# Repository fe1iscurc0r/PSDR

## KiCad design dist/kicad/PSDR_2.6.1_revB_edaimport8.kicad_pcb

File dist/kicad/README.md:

# PSDR 2.6.1 KiCad schematic

KiCad 10 schematic for the PSDR 2.6.1 main board (STM32F746/F429 HF SDR,
0-35 MHz). It is generated from the 2.6.1 PADS Layout ASCII netlist and laid
out one sheet per page of the 2016-07-31 schematic PDF.

## Why this exists

`master` ships the PADS Logic/Layout binaries (`Hardware/PSDR.sch`,
`Hardware/PSDR.pcb`) and an 8-page 2014 schematic PDF. The 2.6.1 ASCII
(`Hardware/PSDR.asc`) and the 10-page 2016 PDF are only on `PSDR_Rebuild` /
`PSDR_F7` / `PSDR_F7_DMA` at `468dc41`. No KiCad-native schematic existed, so
the design could not be opened, searched or checked without PADS.

## What it is, and what it is not

Every pin gets a global label carrying its PADS net name, placed exactly at the
pin endpoint. Pins with no net get a no-connect flag. There are **no wires**:
the connectivity is carried entirely by labels.

This is a **connectivity model, not redrawn artwork**. Trace shapes, symbol
graphics and the designer's margin notes live only in
`Hardware/PSDR_2.6.1_Schematic_2016-07-31.pdf` (page N here corresponds to PDF
page N). It is meant to be read next to that PDF, and to make the netlist
machine-checkable.

## Contents

| File | Contents |
|---|---|
| `PSDR_2.6.1.kicad_sch` | Root sheet, A2, nine hierarchical sheets |
| `PSDR_2.6.1-p02..p10.kicad_sch` | One sheet per PDF page, 391 parts total |
| `PSDR_2.6.1.kicad_sym` | 57 reconstructed symbols (one per PADS part type) |
| `PSDR_2.6.1.kicad_pro`, `sym-lib-table` | Project and symbol library wiring |
| `../netlist/PSDR_2.6.1_netlist.csv` | `net,refdes,pin,pin_name,part_type`, 1132 rows |
| `../netlist/PSDR_2.6.1_netlist.json` | Same data plus the 41 unconnected pins |

Page map: 2 MCU/GPS/USB, 3 clock (Si5338), 4 analog switches/drivers,
5 RX/TX baseband, 6 audio/microphone, 7 UI paddles/LEDs/LCD, 8 power,
9 RF front end, 10 variable filter. PDF page 1 carries notes only, so there is
no sheet for it.

## Regenerating

Requires Python 3 (standard library only) and KiCad 10 for the checks.

```
python tools/pads_asc_to_kicad.py --asc Hardware/PSDR.asc \
    --pdf Hardware/PSDR_2.6.1_Schematic_2016-07-31.pdf \
    --out dist/kicad
```

UUIDs are derived with `uuid5(NAMESPACE_URL, "psdr261/...")`, so the same input
produces byte-identical output; a diff after regeneration is a real change.

`--pcb FILE` optionally copies the footprint field from a `.kicad_pcb` (the
PADS decal name, e.g. `PSDR_PADS:CAP_0603`). Without it that one property is
empty; nothing else changes (391 lines out of ~104000). The board itself is
not part of this change: `.emn`/`.emp` carry only outline, holes and placement,
so the reconstructed board has no pads for 366 of 391 parts and no routing.

## Verification

```
python tools/pads_asc_netlist.py Hardware/PSDR.asc \
    --csv dist/netlist/PSDR_2.6.1_netlist.csv \
    --json dist/netlist/PSDR_2.6.1_netlist.json

kicad-cli sch export netlist --format kicadxml -o out.xml dist/kicad/PSDR_2.6.1.kicad_sch
python tools/kicad_netlist_compare.py --pads dist/netlist/PSDR_2.6.1_netlist.json --kicad out.xml

python tools/kicad_sch_geomcheck.py dist/kicad/PSDR_2.6.1.kicad_sch
kicad-cli sch erc --severity-all dist/kicad/PSDR_2.6.1.kicad_sch
```

Results:

- Netlist: 278 of 278 PADS nets have identical pin sets, 1132 of 1132 connected
  pins are covered, 0 nets only on one side, 0 pins in more than one net,
  391 components. The comparison is a partition check, not a name check, so a
  short between two nets fails it.
- Geometry: no two connection points coincide in any of the 10 files (1173
  points = 1132 labels + 41 no-connects). This is checked separately because
  KiCad silently merges coincident pins and the netlist export would not show it.
- ERC: 0 errors, 391 warnings, all `footprint_link_issues` because the
  `PSDR_PADS` footprint library is deliberately not shipped.
- Names: 276 of 278 match character for character. The other two differ only by
  the PADS overbar escape: `AUDIO_AMP_\SHDN` -> `AUDIO_AMP_~{SHDN}`,
  `\EARPHONE_INSERTED` -> `~{EARPHONE_INSERTED}`.

The exported XML netlist differs between runs only in its `<date>` element.

## Known limits

- Eleven one-pin test pads have ambiguous refdes text in the PDF (`+`, `-`,
  `1PPS`, `CLK`, `DAC1`, `DAC2`, `GND`, `LIPO`, `NRST`, `SCL`, `SDA`). They are
  placed in a strip at the bottom of their page. Connectivity is unaffected: the
  netlist is keyed by refdes, not by position.
- No hierarchical sheet pins. Global labels already connect across sheets.
- No footprint library is shipped, hence the 391 ERC warnings.

## Provenance

- `Hardware/PSDR.asc`: PSDR 2.6.1 PADS Layout ASCII, upstream `468dc41`
  (`Hardware/PSDR.asc`).
- `Hardware/PSDR_2.6.1_Schematic_2016-07-31.pdf`: upstream `468dc41`
  (`Hardware/PSDR Schematic.pdf`), 10 pages, `CreationDate` 2016-07-26.
- Netlist extraction and the sheet layout follow the rules in
  `tools/pads_asc_netlist.py` and `tools/pads_asc_to_kicad.py`.

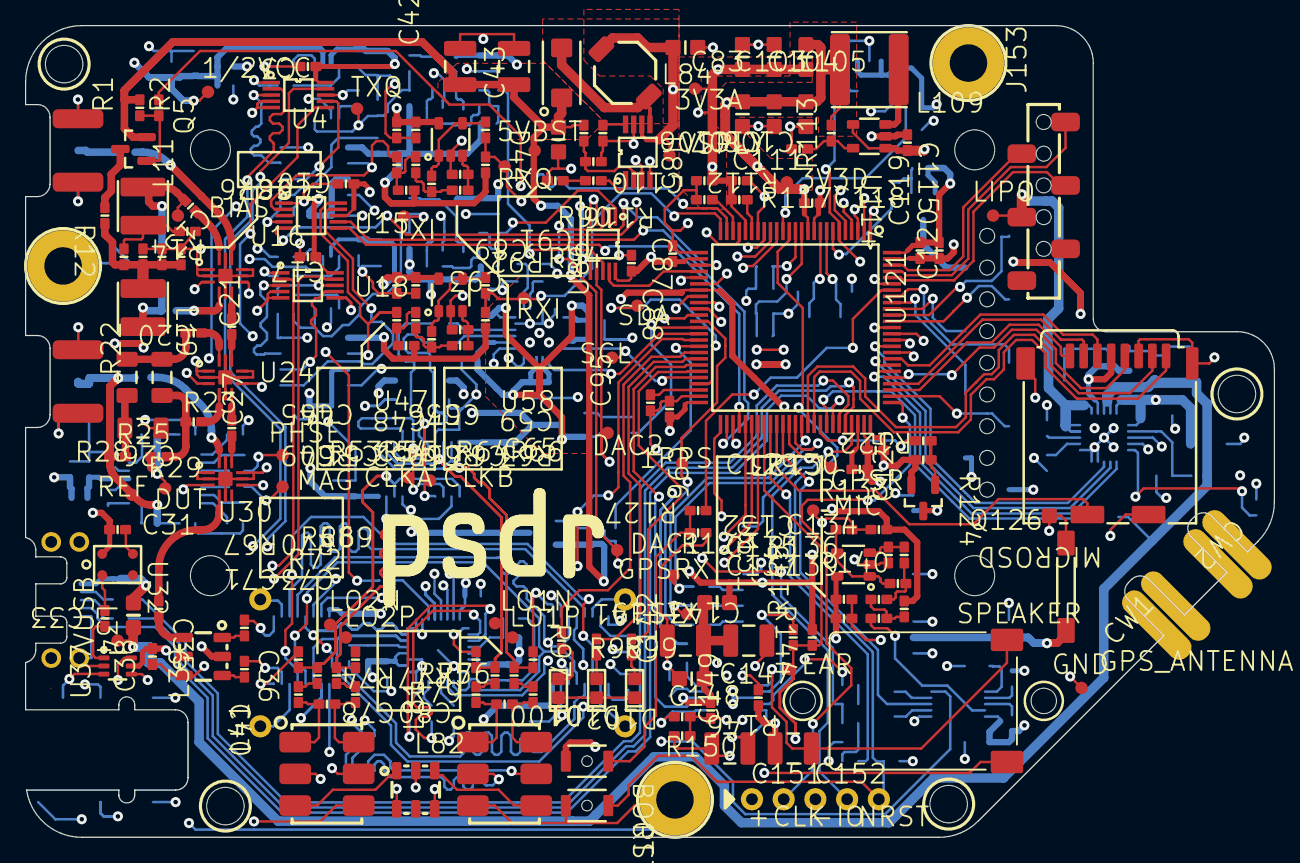
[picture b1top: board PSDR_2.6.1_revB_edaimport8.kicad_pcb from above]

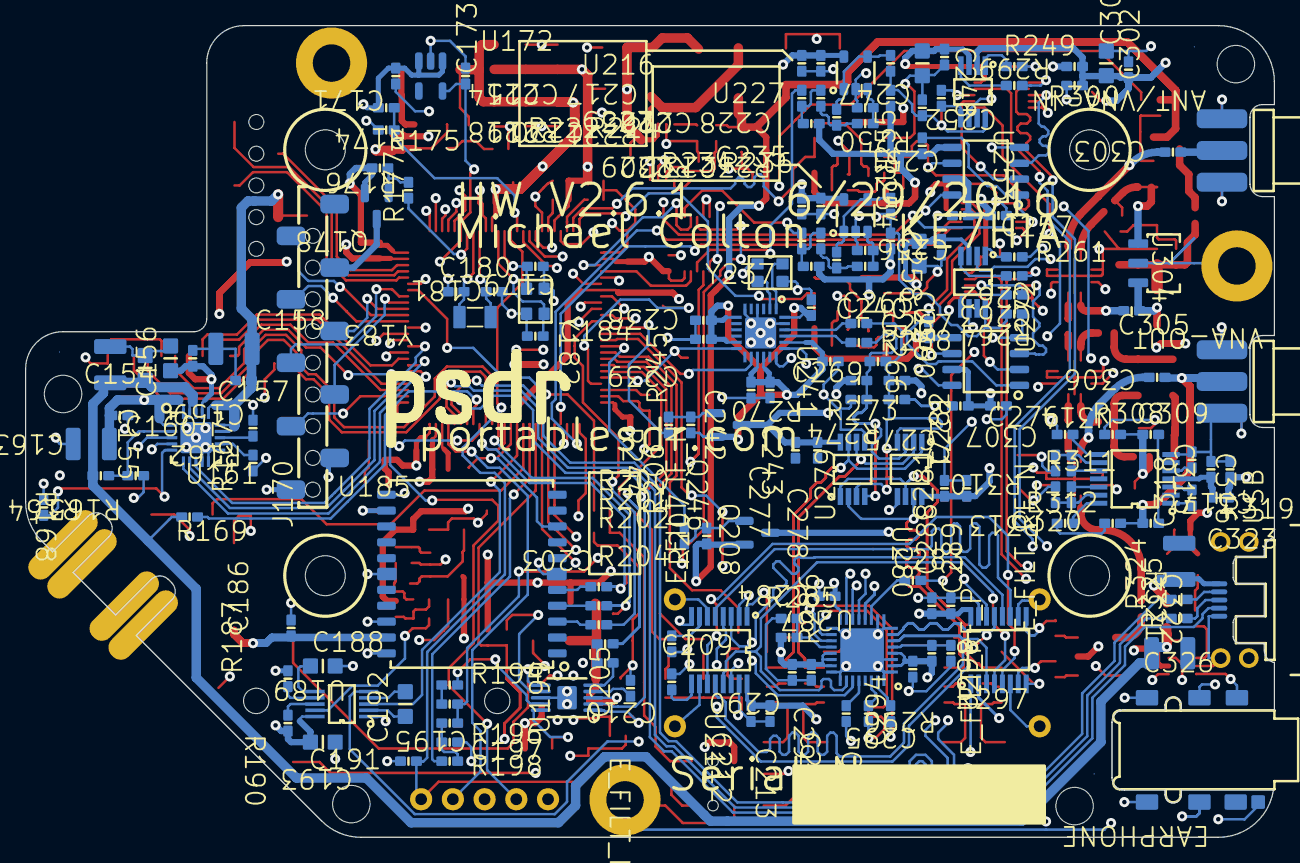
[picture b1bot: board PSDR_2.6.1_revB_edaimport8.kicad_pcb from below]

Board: 4 copper layers, 100.0 x 65.0 mm, 391 parts (182 on the bottom side), 277 nets.

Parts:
1/2VCC, 1PPS, 3V3A, 3V3D, 5VBST: PAD_1MM
+: 0.1in_1PIN
-: 0.1in_1PIN
ANT/VNA-IN: SMA_BOARD_EDGE
BIAS: PAD_1MM
BOOT: BUTTON_B3U-1000P-B
C3, C7, C8, C9, C10, C13, C17, C20, C21, C26, C27, C31, C33, C35, C36, C38, C40, C45, C46, C48, C49, C51, C54, C56, C57, C59, C60, C62, C65, C71, C73, C78, C80, C87, C88, C91, C93, C95, C96, C110, C111, C115, C118, C119, C120, C123, C125, C129, C132, C134, C135, C137, C139, C148, C149, C157, C159, C160, C171, C173, C179, C180, C181, C184, C186, C193, C195, C197, C203, C205, C209, C210, C212, C213, C214, C215, C217, C218, C220, C223, C225, C226, C228, C229, C231, C235, C238, C239, C240, C242, C243, C248, C251, C252, C256, C257, C259, C262, C263, C265, C267, C269, C275, C276, C277, C278, C281, C282, C283, C284, C288, C289, C290, C291, C292, C293, C294, C295, C302, C303, C305, C306, C307, C309, C315, C316, C317, C318, C320, C322: CAP_0603
C42, C43, C142, C143, C151, C152, C154, C158, C163, C323, C326: CSM-X5R-22U-20P-10V-1210
C83: CSM-X5R-10U0-10P-10V-0805
C89, C103, C104, C106, C107, C108, C156: CAP_0805
C147, C155, C188, C191, C192, C247, C258: CSM-X5R-10U0-10P-25V-0805
C301: CSM-X5R-47U-20P-6V3-0805
CLK: 0.1in_1PIN
CLKA: PAD_1MM
CLKB: PAD_1MM
CW1, CW2: MORSE_PADDLE_CONTACTS
D44: DIODE-SMA
D100, D101, D102: LED_0603
DAC1, DAC2: PAD_1MM
DUT: PAD_1MM
EAR: PAD_1MM
EARPHONE: 3.5MM_PHONO_4P_3SW_SJ-42617-SMT
E_FILT_IF_N: 0.1in_1PIN
E_FILT_IF_P: 0.1in_1PIN
E_FILT_RF_N: 0.1in_1PIN
E_FILT_RF_P: 0.1in_1PIN
F1, F2, F3, F4, F5, F6: FIDUCIAL_1MM
GND: PAD_1MM
GPSR: PAD_1MM
GPSRX: PAD_1MM
GPSTX: PAD_1MM
GPS_ANTENNA: GPS_ANTENNA-W3062A
IO: 0.1in_1PIN
J153: 0.1in_6P_HEADER_DUAL_ENTRY_1241152-6
J170: SPI_LCD_BOTTOM_ENTRY
L11, L19: IND_SMT_220UH_SRN4018-221M
L34, L105, L141: ISM-0805-10U
L39, L82: BALUN_1-2_WBC2-1TL
L41, L81: MIXER_DIODE-RING_ADE-2ASK
L84: IND_4.7UH_SMT_CDRH4D28CNP-4R7PC
L109: 2U2H_INDUCTOR_NR6028T2R2N
LIPO: PAD_1MM
LO1N, LO1P, LO2N, LO2P: PAD_1MM
M1, M2, M3: MH3M_PLATED
M4, M5, M6, M7: MH3M
MAG: PAD_1MM
MIC: PAD_1MM
MICROSD: MICROSD_DM3CS-SF
NRST: 0.1in_1PIN
PHSE: PAD_1MM
Q5, Q126, Q178, Q208, Q246: MOSFET_P_SOT23_IRLML6401
R1, R2, R6, R12, R14, R28, R29, R50, R52, R53, R55, R61, R63, R64, R66, R67, R68, R69, R70, R72, R74, R75, R76, R77, R79, R90, R92, R94, R97, R98, R99, R112, R113, R116, R117, R122, R124, R127, R128, R130, R133, R136, R140, R144, R145, R146, R150, R162, R164, R165, R167, R168, R169, R174, R175, R176, R177, R187, R190, R194, R196, R198, R200, R201, R202, R204, R206, R207, R219, R221, R222, R224, R230, R232, R234, R236, R244, R245, R249, R250, R254, R261, R264, R266, R268, R270, R271, R273, R274, R285, R286, R296, R297, R299, R300, R308, R310, R311, R312, R313, R319, R321, R324, R325: RES_0603
R22, R23, R25: RSM-6K98-1PCT-250MW-1206
REF: PAD_1MM
RST: BUTTON_B3U-1000P-B
RXI: PAD_1MM
RXQ: PAD_1MM
SCL: PAD_1MM
SDA: PAD_1MM
SPEAKER: SPEAKER_SMT_WATERPROOF_2403-260-00107
TXI: PAD_1MM
TXQ: PAD_1MM
U4, U18, U86: DPDT_ANALOG_MAX4525
U15: DIGITAL_POT_MAX5388
U16, U24, U30: RF_DPDT_MASWSS0129TR
U32: MICROPHONE_MEMS_SPU0410HR5H-PB
U37: SPDT_ANALOG_SWITCH_SN74LVC1G3157
U47, U58, U131, U216, U227: OP_AMP_FAN4174
U85: BOOST_REG_ADP1613
U114: BUCK_REGULATOR_AP3417C
U121: STM32F746_LQFP100
U161: BAT-MANAGE_MCP73871
U172: 3V3_LDO_MCP1802
U185: GPS_MODULE_RXM-GPS-RM-T
U189: MIC_PREAMP_SSM2167
U199: AUDIO_AMP_TPA0253DGQR
U211, U298: 74CBTLV3253
U241: SI5338
U253, U260: AD8131
U255, U272: MCP6N11
U279, U280: SY10EP52V
U287: VARIABLE_FILTER_HMC1023
U304: MMIC-AMP_HMC482ST
U314: AD8302
USB: MICROUSB_H12192CT-ND
VNA-OUT: SMA_BOARD_EDGE
VSPLY: PAD_1MM
VUSB: PAD_1MM
X1, X2: MH_80M
Y182, Y237: CRYSTAL3225
Y183: CRYSTAL_SMT_32.768

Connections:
5V_REG_ENABLE: U85.3, U121.1
$$$484: Q126.1, R122.1, R124.1
$$$596: R312.1, R313.2, U314.13
$$$598: R22.1, R25.2, R28.2
$$$618: Q178.1, R176.1, R177.2
$$$1054: C316.2, R319.1, U314.4
$$$1603: C322.2, U314.2
$$$1611: C309.2, U314.6
$$$1679: C188.1, U189.6
$$$1694: C318.2, U314.3
$$$1701: C315.2, U314.5
$$$1734: C192.2, U189.4
$$$1740: C192.1, U189.2
$$$2458: C320.2, U314.14
$$$2472: C307.1, U314.8
$$$2878: R311.1, U314.10
$$$2881: R310.1, R311.2, U314.9
$$$2891: R313.1, U314.12
$$$2987: C197.1, R196.1, R198.2
$$$3254: R190.1, U189.8
$$$3258: R187.1, U189.7
$$$4060: Q5.1, R1.2, R2.2
$$$5312: C139.2, R136.1, R140.1
$$$5393: U241.2, Y237.1
$$$5395: U241.1, Y237.3
$$$5476: C134.2, R133.1, R136.2
$$$5477: E_FILT_IF_P.1, U211.10
$$$5480: E_FILT_IF_N.1, U211.6
$$$5486: E_FILT_RF_P.1, U298.6
$$$5490: E_FILT_RF_N.1, U298.10
$$$5502: C132.1, R133.2, U131.3
$$$5510: C265.1, U241.22
$$$5513: C267.1, U241.21
$$$5711: C129.1, C134.1, U131.1, U131.4
$$$5934: LO1N.1, R74.2, R75.2, U279.6, U280.2
$$$5936: LO2P.1, R69.2, R70.2, U279.2, U280.7
$$$5937: LO2N.1, R67.2, R68.2, U279.1, U280.6
$$$5939: LO1P.1, R76.2, R77.2, U279.7, U280.1
$$$8723: L41.3, L82.1
$$$8785: L81.4, L82.3
$$$8887: C148.1, U199.1
$$$9133: Q208.1, R206.1, R207.2
$$$9448: L41.5, U4.9
$$$9458: L41.2, U4.2
$$$9485: L81.5, U18.9
$$$9489: L81.2, U18.2
$$$9652: R194.2, U199.9
$$$9661: R204.2, U199.5
$$$9712: C195.2, R194.1
$$$9714: C203.2, R204.1
$$$9819: C152.2, EARPHONE.3, R146.2
$$$9979: EARPHONE.10, SPEAKER.2
$$$10136: C152.1, SPEAKER.1, U199.6
$$$10265: R144.2, U199.7
$$$10468: C205.1, U199.4
$$$10534: D101.1, R98.1
$$$11822: C151.1, U199.10
$$$11833: C151.2, EARPHONE.2, R150.1
$$$11912: R249.1, U253.1
$$$11915: R261.1, U260.1
$$$12053: C323.2, L34.2, USB.1
$$$13766: C33.1, U32.4
$$$14035: C142.2, C143.2, C147.2, C149.1, L141.2, U199.3
$$$14589: R90.1, R92.2, U85.2
$$$14676: C91.1, U85.8
$$$14686: C93.1, R94.1
$$$14690: R94.2, U85.1
$$$15374: C13.1, U16.12
$$$15375: C303.2, U16.10
$$$15378: C305.1, U16.4
$$$15380: C21.1, U16.6
$$$15644: C283.1, U287.11
$$$15845: C262.2, U260.4
$$$15873: C263.2, U260.5
$$$15926: C252.2, U253.4
$$$15997: C251.2, U253.5
$$$16013: C35.1, L39.6
$$$16059: C21.2, U24.10
$$$16062: C20.1, U24.12
$$$16064: C26.1, U24.4
$$$16065: C27.1, U24.6
$$$16344: C40.2, U298.7
$$$16346: C36.2, U298.9
$$$16399: R164.1, R165.2, U161.2
$$$16411: C210.2, U211.9
$$$16416: C209.2, U211.7
$$$16521: D100.1, R97.1
$$$16999: C35.2, U30.4
$$$17003: C306.2, U30.12
$$$17006: C27.2, U30.10
$$$18814: R168.2, U161.5
$$$19175: R162.2, U161.13
$$$19436: R167.2, U161.12
$$$21746: R202.1, U185.3
$$$21752: R200.1, U185.5
$$$21776: R201.1, U185.4
$$$22336: ANT/VNA-IN.1, C303.1
$$$22472: Q246.1, R244.1, R245.2
$$$22801: R324.1, USB.2
$$$22806: R325.1, USB.3
$$$22983: Q126.3, U185.12
$$$23052: J170.8, Q178.3
$$$23761: C125.1, U121.73
$$$23762: C179.2, U121.13, Y182.1
$$$23763: C184.2, U121.12, Y182.3
$$$23764: C181.2, U121.9, Y183.1
$$$23765: C180.2, U121.8, Y183.2
$$$23766: C95.1, U121.48
$$$23767: R117.2, U121.20
$$$24763: R112.1, R113.2, U114.5
$$$24779: L109.2, U114.3
$$$26276: BOOT.1, R127.2, R128.1
$$$26619: D102.1, R99.1
$$$27752: R296.1, R297.2, U287.5
$$$27784: R285.2, R286.1, U287.20
$$$28367: C186.1, GPS_ANTENNA.1, U185.19
$$$28421: C48.1, C54.2, U47.1, U47.4
$$$28422: C54.1, R50.2, R55.1
$$$28423: C51.1, R55.2, U47.3
$$$28424: C49.2, R50.1, R53.1
$$$28425: C59.1, C65.2, U58.1, U58.4
$$$28426: C65.1, R61.2, R66.1
$$$28427: C62.1, R66.2, U58.3
$$$28428: C60.2, R61.1, R64.1
$$$28429: C228.1, C235.2, U227.1, U227.4
$$$28430: C235.1, R230.2, R236.1
$$$28431: C231.1, R236.2, U227.3
$$$28432: C229.2, R230.1, R234.1
$$$28433: C217.1, C223.2, U216.1, U216.4
$$$28434: C223.1, R219.2, R224.1
$$$28435: C220.1, R224.2, U216.3
$$$28436: C218.2, R219.1, R222.1
$$$28948: Q5.3, R12.2
$$$31361: L11.2, R6.1, R14.2
$$$31407: C267.2, CLKB.1, R268.1, R270.1, R273.2, U279.4, U280.3
$$$31408: C265.2, CLKA.1, R268.2, R271.1, R274.2, U279.3, U280.4
$$$31737: C71.1, R68.1
$$$31740: C293.2, U287.18
$$$31745: C293.1, U287.30
$$$31748: C294.2, U287.31
$$$31750: C294.1, U287.19
$$$31767: C80.1, R76.1
$$$31769: C78.1, R75.1
$$$31771: C73.1, R69.1
$$$32279: U211.11, U298.5
$$$32286: U211.5, U298.11
+3V3: 3V3A.1, C3.1, C17.1, C31.1, C38.1, C45.1, C46.1, C56.1, C57.1, C103.1, C104.1, C110.1, C111.1, C135.1, C137.1, C191.1, C212.1, C213.1, C214.1, C215.1, C225.1, C226.1, C247.1, C248.1, C256.1, C257.1, C258.1, C259.1, C275.1, C276.1, C288.1, C289.1, C317.2, L105.1, R117.1, R187.2, R190.2, R270.2, R271.2, R299.2, R319.2, U4.10, U18.10, U32.1, U37.5, U47.5, U58.5, U121.21, U131.5, U189.10, U211.16, U216.5, U227.5, U253.3, U255.7, U260.3, U272.7, U298.16
+3V3_CPU: 3V3D.1, +.1, BOOT.2, C10.1, C87.1, C88.1, C96.1, C106.1, C107.1, C108.1, C118.1, C119.1, C120.1, C123.1, C156.1, C157.1, C238.1, C239.1, C240.1, C242.1, C243.1, C269.1, J170.1, L105.2, L109.1, L141.1, MICROSD.4, Q126.2, Q178.2, Q246.2, R113.1, R124.2, R145.1, R176.2, R245.1, U15.8, U86.10, U121.11, U121.27, U121.50, U121.75, U121.100, U161.4, U161.17, U241.7, U241.11, U241.15, U241.16, U241.20, U241.24
+3V3_FLIP_FLOP: C277.1, C278.1, C281.1, C282.1, Q246.3, U279.8, U280.8
+5V: C154.1, C155.2, C326.2, L34.1, R164.2, R169.1, U161.18, U161.19, VUSB.1
+5V_AMP: C7.2, C8.2, C9.2, L19.2, R6.2, R12.1
+5V_BOOST: 5VBST.1, C42.2, C43.2, C89.1, D44.1, Q5.2, Q208.2, R1.1, R90.2, R207.1
AMP_POWER: R2.1, U121.2
AMP_SWITCH_A: U16.3, U121.22
AMP_SWITCH_B: U16.7, U121.5
AUDIO_AMP_SHDN: U121.44, U199.2
BOOST_LOOP: D44.2, L84.2, U85.5
BOOT0: R127.1, U121.94
BOOT1: R116.1, U121.23
BUILT-IN_MIC_OUT: C33.2, U37.1
CHARGE_SOURCE: U121.95, U161.3
CHARGE_STATUS2: U121.82, U161.7
DAC1: U86.2, U121.28
DAC1_TO_RF: C229.1, U86.1
DAC1_TO_SPEAKER: C195.1, DAC1.1, R196.2, U86.3
DAC2: U86.9, U121.29
DAC2_TO_RF: C218.1, U86.8
DAC2_TO_SPEAKER: C203.1, DAC2.1, U86.7
DAC_MUX: U86.6, U121.3
EARPHONE_INSERTED: EAR.1, EARPHONE.11, R144.1, R145.2, U121.58
ENC_A: J153.2, U121.98
ENC_B: J153.1, U121.97
ENC_SW: J153.3, U121.96
EXT_MIC_OUT: EARPHONE.4, U37.3, U121.56
FILTER/GAIN_POT_CLK: U15.7, U121.52, U287.12
FILTER/GAIN_POT_MOSI: U15.6, U121.54, U287.14
FILTER_CAL: C283.2, U241.18
FILTER_CS: U121.51, U287.15
FILTER_IF_N: C209.1, L82.6
FILTER_IF_P: C210.1, L82.4
FILTER_IN_N: U211.3, U287.27, U298.12
FILTER_IN_P: U211.13, U287.26, U298.4
FILTER_MISO: U121.53, U287.13
FILTER_OUT_N: U211.4, U287.7, U298.13
FILTER_OUT_P: U211.12, U287.6, U298.3
FILTER_RF_N: C36.1, L39.1
FILTER_RF_P: C40.1, L39.3
FILTER_S0: U121.40, U211.14, U298.14
FILTER_S1: U121.55, U211.2, U298.2
FLIP-FLOP_POWER: R244.2, U121.38
F_SYNTH_CAL: U121.39, U241.14
GAIN_POT_NSS: U15.5, U121.4
GND: -.1, ANT/VNA-IN.2, ANT/VNA-IN.3, ANT/VNA-IN.4, ANT/VNA-IN.5, C3.2, C7.1, C8.1, C9.1, C10.2, C17.2, C31.2, C38.2, C42.1, C43.1, C45.2, C46.2, C51.2, C56.2, C57.2, C62.2, C83.2, C87.2, C88.2, C89.2, C91.2, C93.2, C95.2, C96.2, C103.2, C104.2, C106.2, C107.2, C108.2, C110.2, C111.2, C115.2, C118.2, C119.2, C120.2, C123.2, C125.2, C132.2, C135.2, C137.2, C142.1, C143.1, C147.1, C148.2, C149.2, C154.2, C155.1, C156.2, C157.2, C158.2, C159.2, C160.2, C163.1, C171.2, C173.2, C179.1, C180.1, C181.1, C184.1, C186.2, C188.2, C191.2, C193.2, C197.2, C205.2, C212.2, C213.2, C214.2, C215.2, C220.2, C225.2, C226.2, C231.2, C238.2, C239.2, C240.2, C242.2, C243.2, C247.2, C248.2, C256.2, C257.2, C258.2, C259.2, C269.2, C275.2, C276.2, C277.2, C278.2, C281.2, C282.2, C284.2, C288.2, C289.2, C290.2, C291.2, C292.2, C295.2, C301.2, C302.2, C307.2, C315.1, C316.1, C317.1, C318.1, C320.1, C323.1, C326.1, D100.2, D101.2, D102.2, EARPHONE.1, GND.1, GPS_ANTENNA.2, J153.5, J170.2, L39.4, L41.4, L81.3, L82.2, M1.1, M2.1, M3.1, MICROSD.6, MICROSD.9, MICROSD.10, MICROSD.11, MICROSD.13, R14.1, R25.1, R67.1, R70.1, R74.1, R77.1, R92.1, R112.2, R116.2, R128.2, R146.1, R150.2, R162.1, R165.1, R167.1, R168.1, R175.1, R249.2, R250.1, R261.2, R264.1, R273.1, R274.1, R285.1, R297.1, R300.1, R308.1, R321.1, RST.2, U4.4, U4.5, U15.1, U16.1, U16.2, U16.5, U16.8, U16.9, U16.11, U16.13, U18.4, U18.5, U24.1, U24.2, U24.5, U24.8, U24.9, U24.11, U24.13, U30.1, U30.2, U30.5, U30.8, U30.9, U30.11, U30.13, U32.2, U32.3, U37.2, U47.2, U58.2, U85.4, U85.7, U86.4, U86.5, U114.2, U121.10, U121.19, U121.26, U121.49, U121.74, U121.99, U131.2, U161.9, U161.10, U161.11, U161.21, U172.2, U185.18, U185.20, U185.21, U185.22, U189.1, U199.8, U199.11, U211.1, U211.8, U211.15, U216.2, U227.2, U241.4, U241.6, U241.23, U241.25, U253.6, U255.4, U260.6, U272.4, U279.5, U280.5, U287.1, U287.3, U287.8, U287.9, U287.10, U287.17, U287.24, U287.25, U287.32, U287.33, U298.1, U298.8, U298.15, U304.2, U314.1, U314.7, USB.5, USB.6, USB.7, USB.8, USB.9, VNA-OUT.2, VNA-OUT.3, VNA-OUT.4, VNA-OUT.5, Y182.2, Y182.4, Y237.2, Y237.4
GPS_POWER: R122.2, U121.67
GPS_PPS: 1PPS.1, R202.2, U121.37
GPS_RESET: GPSR.1, U121.62, U185.8
HALF_VCC: 1/2VCC.1, C301.1, C302.1, L39.2, R52.2, R53.2, R63.2, R64.2, R130.2, R140.2, R221.2, R222.2, R232.2, R234.2, R254.2, R266.2, R299.1, R300.2, U121.32, U253.2, U255.5, U260.2, U272.5
I2C_SCL: SCL.1, U121.46, U241.12
I2C_SDA: SDA.1, U121.47, U241.19
IMP_BRIDGE_IN: C20.2, R22.2, R23.2
IMP_BRIDGE_OUT: C26.2, R23.1, R29.2
IMP_BRIDGE_SWITCH_A: U24.3, U121.16
IMP_BRIDGE_SWITCH_B: U24.7, U121.30
INAMP_ENABLE: U121.17, U255.8, U272.8
JTCK/SWCLK: CLK.1, U121.76
JTMS/SWDIO: IO.1, U121.72
LCD_CS: J170.3, U121.77
LCD_DC/RS: J170.5, U121.93
LCD_LED: R177.1, U121.7
LCD_MISO: J170.9, U121.90
LCD_MOSI: J170.6, U121.91
LCD_RESET: J170.4, U121.92
LCD_SCK: J170.7, U121.89
LED_2: R98.2, U121.43
LED_3: R99.2, U121.45
LED_WHITE: R97.2, U121.42
LIPO: C158.1, C159.1, C171.1, J153.4, LIPO.1, R174.2, U161.14, U161.15, U161.16, U172.1, U172.3
LIPO_V: R174.1, R175.2, U121.15
LOW_BAT: U121.85, U161.8
LPF_5V: C284.1, C290.1, C291.1, C292.1, C295.1, Q208.3, R286.2, R296.2, U287.2, U287.4, U287.16, U287.21, U287.22, U287.23, U287.28
LPF_POWER: R206.2, U121.41
MAGNITUDE: MAG.1, R312.2, U121.34
MIC_AMP_OUT: C139.1, U189.9
MIC_FILTER_OUT: C129.2, MIC.1, R130.1, U121.35
MIC_OUT: U37.4, U189.5
MIC_SELECT: U37.6, U121.57
MIXER_LO1N: C78.2, L81.1, R79.1
MIXER_LO1P: C80.2, L81.6, R79.2
MIXER_LO2N: C71.2, L41.1, R72.1
MIXER_LO2P: C73.2, L41.6, R72.2
NRST: C193.1, NRST.1, RST.1, U121.14
OP_GAIN_A_WP: R266.1, U15.9, U272.1
OP_GAIN_B_WP: R254.1, U15.4, U255.1
PADDLE_INDEX_NC: CW2.1, U121.87
PADDLE_INDEX_NO: CW2.2, U121.88
PADDLE_THUMB_NC: CW1.1, U121.86
PADDLE_THUMB_NO: CW1.2, U121.84
PHASE: PHSE.1, R310.2, U121.33
POWER_GOOD: U121.81, U161.6
PREAMP_SHTDWN: U121.61, U189.3
RF_AMP_IN: BIAS.1, C13.2, L11.1, U304.1
RF_AMP_OUT: C305.2, L19.1, U304.3
RF_ANT: C309.1, DUT.1, R29.1, R308.2
RF_REF: C306.1, C322.1, R28.1, R321.2, REF.1, VNA-OUT.1
RX-I_FILTERED: C48.2, R52.1, RXI.1, U121.25
RX-I_INAMP_N: U18.7, U272.2
RX-I_INAMP_P: U18.3, U272.3
RX-I_UNFILTERED/OP_GAIN_A_L: C49.1, U15.10, U272.6
RX-Q_FILTERED: C59.2, R63.1, RXQ.1, U121.24
RX-Q_INAMP_N: U4.7, U255.2
RX-Q_INAMP_P: U4.3, U255.3
RX-Q_UFILTERED/OP_GAIN_B_L: C60.1, U15.2, U255.6
RX_TO_GPS: GPSRX.1, R200.2, U121.63
SDIO_CLK: MICROSD.5, U121.80
SDIO_CMD: MICROSD.3, U121.83
SDIO_DAT0: MICROSD.7, U121.65
SDIO_DAT1: MICROSD.8, U121.66
SDIO_DAT2: MICROSD.1, U121.78
SDIO_DAT3: MICROSD.2, U121.79
SD_CARD_DETECT: MICROSD.12, U121.60
SIDETONE: R198.1, U121.59
TRX_SWITCH: U4.6, U18.6, U121.18
TX-I_DRIVER_N: C263.1, U18.8
TX-I_DRIVER_P: C262.1, U18.1
TX-I_FILTERED: C228.2, R232.1, R264.2, TXI.1, U260.8
TX-Q_DRIVER_N: C251.1, U4.8
TX-Q_DRIVER_P: C252.1, U4.1
TX-Q_FILTERED: C217.2, R221.1, R250.2, TXQ.1, U253.8
TX_FROM_GPS: GPSTX.1, R201.2, U121.64
TX_RF_SWITCH_A: U30.3, U121.36
TX_RF_SWITCH_B: U30.7, U121.31
USB_D+: R325.2, U121.71
USB_D-: R324.2, U121.70
USB_ID: U121.69, USB.4
USB_VBUS: R169.2, U121.68
VBAT_BKP: C173.1, U121.6, U172.5, U185.11
V_SUPPLY: C83.1, C115.1, C160.1, C163.2, L84.1, U85.6, U114.1, U114.4, U161.1, U161.20, VSPLY.1

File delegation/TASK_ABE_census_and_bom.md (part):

# TASKS A/B/E - every distinct part on the board, and the DigiKey-numbered BOM rows

A = lifecycle status per line, B = LCSC/SMT usability, E = the official
datasheet URL + revision + page for each part type you are asked about.

## 1. part census (part_type, qty, category, designators)

Passive part-type names encode the value, e.g.
`CSM-X5R-22U-20P-10V-1210` = 22 uF X5R 20% 10 V 1210,
`RSM-6K98-1PCT-250MW-1206` = 6.98 kOhm 1% 250 mW 1206.

```csv
part_type,qty,category,designators
CAP_0603,130,passive,"C10,C110,C111,C115,C118,C119,C120,C123,C125,C129,C13,C132,C134,C135,C137,C139,C148,C149,C157,C159,C160,C17,C171,C173,...(of 130)"
RES_0603,104,passive,"R1,R112,R113,R116,R117,R12,R122,R124,R127,R128,R130,R133,R136,R14,R140,R144,R145,R146,R150,R162,R164,R165,R167,R168,...(of 104)"
PAD_1MM,33,ic_or_other,"1/2VCC,1PPS,3V3A,3V3D,5VBST,BIAS,CLKA,CLKB,DAC1,DAC2,DUT,EAR,GND,GPSR,GPSRX,GPSTX,LIPO,LO1N,LO1P,LO2N,LO2P,MAG,MIC,PHSE,...(of 33)"
CSM-X5R-22U-20P-10V-1210,11,passive,"C142,C143,C151,C152,C154,C158,C163,C323,C326,C42,C43"
"0.1""_1PIN",9,ic_or_other,"+,-,CLK,E_FILT_IF_N,E_FILT_IF_P,E_FILT_RF_N,E_FILT_RF_P,IO,NRST"
CAP_0805,7,passive,"C103,C104,C106,C107,C108,C156,C89"
CSM-X5R-10U0-10P-25V-0805,7,passive,"C147,C155,C188,C191,C192,C247,C258"
FIDUCIAL_1MM,6,ic_or_other,"F1,F2,F3,F4,F5,F6"
MOSFET_P_SOT23_IRLML6401,5,ic_or_other,"Q126,Q178,Q208,Q246,Q5"
OP_AMP_FAN4174,5,ic_or_other,"U131,U216,U227,U47,U58"
MH3M,4,ic_or_other,"M4,M5,M6,M7"
DPDT_ANALOG_MAX4525,3,ic_or_other,"U18,U4,U86"
ISM-0805-10U,3,passive,"L105,L141,L34"
LED_0603,3,ic_or_other,"D100,D101,D102"
MH3M_PLATED,3,ic_or_other,"M1,M2,M3"
RF_DPDT_MASWSS0129TR,3,ic_or_other,"U16,U24,U30"
RSM-6K98-1PCT-250MW-1206,3,passive,"R22,R23,R25"
74CBTLV3253,2,ic_or_other,"U211,U298"
AD8131,2,ic_or_other,"U253,U260"
BALUN_1-2_WBC2-1TL,2,ic_or_other,"L39,L82"
BUTTON_B3U-1000P-B,2,ic_or_other,"BOOT,RST"
CRYSTAL3225,2,ic_or_other,"Y182,Y237"
IND_SMT_220UH_SRN4018-221M,2,passive,"L11,L19"
MCP6N11,2,ic_or_other,"U255,U272"
MH_80M,2,ic_or_other,"X1,X2"
MIXER_DIODE-RING_ADE-2ASK,2,ic_or_other,"L41,L81"
MORSE_PADDLE_CONTACTS,2,ic_or_other,"CW1,CW2"
SMA_BOARD_EDGE,2,ic_or_other,"ANT/VNA-IN,VNA-OUT"
SY10EP52V,2,ic_or_other,"U279,U280"
"0.1""_6P_HEADER_DUAL_ENTRY_1241152-6",1,ic_or_other,J153
2U2H_INDUCTOR_NR6028T2R2N,1,ic_or_other,L109
3.5MM_PHONO_4P_3SW_SJ-42617-SMT,1,ic_or_other,EARPHONE
3V3_LDO_MCP1802,1,ic_or_other,U172
AD8302,1,ic_or_other,U314
AUDIO_AMP_TPA0253DGQR,1,ic_or_other,U199
BAT-MANAGE_MCP73871,1,ic_or_other,U161
BOOST_REG_ADP1613,1,ic_or_other,U85
BUCK_REGULATOR_AP3417C,1,ic_or_other,U114
CRYSTAL_SMT_32.768,1,ic_or_other,Y183
CSM-X5R-10U0-10P-10V-0805,1,passive,C83
CSM-X5R-47U-20P-6V3-0805,1,passive,C301
DIGITAL_POT_MAX5388,1,ic_or_other,U15
DIODE-SMA,1,ic_or_other,D44
GPS_ANTENNA-W3062A,1,ic_or_other,GPS_ANTENNA
GPS_MODULE_RXM-GPS-RM-T,1,ic_or_other,U185
IND_4.7UH_SMT_CDRH4D28CNP-4R7PC,1,passive,L84
MICROPHONE_MEMS_SPU0410HR5H-PB,1,ic_or_other,U32
MICROSD_DM3CS-SF,1,ic_or_other,MICROSD
MICROUSB_H12192CT-ND,1,ic_or_other,USB
MIC_PREAMP_SSM2167,1,ic_or_other,U189
MMIC-AMP_HMC482ST,1,ic_or_other,U304
SI5338,1,ic_or_other,U241
SPDT_ANALOG_SWITCH_SN74LVC1G3157,1,ic_or_other,U37
SPEAKER_SMT_WATERPROOF_2403-260-00107,1,ic_or_other,SPEAKER
SPI_LCD_BOTTOM_ENTRY,1,ic_or_other,J170
STM32F746_LQFP100,1,ic_or_other,U121
VARIABLE_FILTER_HMC1023,1,ic_or_other,U287
```

## 2. BOM rows that carry a DigiKey number

```csv
qty,digikey,vendor,mpn,octopart_url
Qty,Line Item,Manufacturer,MPN,Octopart URL
2,WM50018-05-ND,Molex,22-28-4054,https://octopart.com/22-28-4054-molex-278278
2,J629-ND,Emerson Network Power,142-0711-821,https://octopart.com/142-0711-821-emerson+network+power-39448276
2,SW1143CT-ND,Omron,B3U-1000P-B,https://octopart.com/b3u-1000p-b-omron-1057356
68,490-3285-1-ND,Murata,GRM188R72A104KA35D,https://octopart.com/grm188r72a104ka35d-murata-196904
4,1276-1008-1-ND,Samsung,CL10C101JB8NNNC,https://octopart.com/cl10c101jb8nnnc-samsung-9299377
5,1276-1009-1-ND,Samsung,CL10B103KB8NNNC,https://octopart.com/cl10b103kb8nnnc-samsung-9299374
15,1276-1113-1-ND,Samsung,CL21B106KQQNNNE,https://octopart.com/cl21b106kqqnnne-samsung-18183217
15,490-1472-1-ND,Murata,GRM188R72A102KA01D,https://octopart.com/grm188r72a102ka01d-murata-196190
7,1276-1946-1-ND,Samsung,CL10B105KP8NNNC,https://octopart.com/cl10b105kp8nnnc-samsung-19831604
11,1276-3375-1-ND,Samsung,CL32A227MQVNNNE,https://octopart.com/cl32a227mqvnnne-samsung-21642163
4,1276-1193-1-ND,Samsung,CL10A226MQ8NRNC,https://octopart.com/cl10a226mq8nrnc-samsung-19018972
5,1276-1134-1-ND,Samsung,CL10B225KP8NNNC,https://octopart.com/cl10b225kp8nnnc-samsung-19831669
1,1276-2030-1-ND,Samsung,CL10B332JB8NNNC,https://octopart.com/cl10b332jb8nnnc-samsung-15492529
1,311-4001-1-ND,Yageo,CC0603JRX7R8BB333,https://octopart.com/cc0603jrx7r8bb333-yageo-25629527
4,1276-1062-1-ND,Samsung,CL10B474KO8NNNC,https://octopart.com/cl10b474ko8nnnc-samsung-9301678
1,1276-2420-1-ND,Samsung,CL21A476MQCLRNC,https://octopart.com/cl21a476mqclrnc-samsung-24871259
4,490-7203-1-ND,Murata,GRM188R61E475KE11D,https://octopart.com/grm188r61e475ke11d-murata-26982327
2,1276-2133-1-ND,Samsung,CL10C060CB8NNNC,https://octopart.com/cl10c060cb8nnnc-samsung-19831802
5,445-14209-1-ND,TDK,C1608X6S1A685K080AC,https://octopart.com/c1608x6s1a685k080ac-tdk-28168623
2,445-14102-1-ND,TDK,C1608NP02A080D080AA,https://octopart.com/c1608np02a080d080aa-tdk-28168516
1,475-2831-1-ND,Osram Opto,LW Q38E-Q1OO-3K6L-1,https://octopart.com/lw+q38e-q1oo-3k6l-1-osram+opto-61925015
1,475-2512-1-ND,Osram Opto,LS Q976-NR-1,https://octopart.com/ls+q976-nr-1-osram+opto-31093944
1,511-1577-1-ND,rohm,SML-D12D8WT86,https://octopart.com/sml-d12d8wt86-rohm-9290841
1,MBRA340T3GOSCT-ND,ON Semiconductor,MBRA340T3G,https://octopart.com/mbra340t3g-on+semiconductor-330950
1,CP-43617SJCT-ND,CUI Devices,SJ-43617-SMT-TR,https://octopart.com/sj-43617-smt-tr-cui+devices-106234256
1,553-2579-1-ND,Pulse,W3062A,https://octopart.com/w3062a-pulse-20005248
1,A107015CT-ND,TE Connectivity,1241152-6,https://octopart.com/1241152-6-te+connectivity-41017930
1,A107013CT-ND,TE Connectivity,1-1241152-0,https://octopart.com/1-1241152-0-te+connectivity-40985157
3,445-173012-1-ND,TDK,VLS201612HBX-2R2M-1,https://octopart.com/vls201612hbx-2r2m-1-tdk-52458620
1,587-2098-1-ND,Taiyo Yuden,NR6028T2R2N,https://octopart.com/nr6028t2r2n-taiyo+yuden-8598465
2,WBC2-1TLB,Coilcraft,WBC2-1TLB,https://octopart.com/wbc2-1tlb-coilcraft-6747758
1,308-2043-1-ND,Sumida,CDRH4D28CNP-4R7PC,https://octopart.com/cdrh4d28cnp-4r7pc-sumida-11543079
2,SRN4018-221MCT-ND,Bourns,SRN4018-221M,https://octopart.com/srn4018-221m-bourns-25452390
2,ADE-2ASK,Mini-Circuits,ADE2ASK+,https://octopart.com/ade2ask%2B-mini-circuits-64850656
1,HR1972CT-ND,Hirose,DM3CS-SF,https://octopart.com/dm3cs-sf-hirose-44525751
5,IRLML6401PBFCT-ND,Infineon,IRLML6401TRPBF,https://octopart.com/irlml6401trpbf-infineon-65874987
11,541-0.0GCT-ND,Vishay,CRCW06030000Z0EA,https://octopart.com/crcw06030000z0ea-vishay-39556096
25,P100KGCT-ND,Panasonic,ERJ-3GEYJ104V,https://octopart.com/erj-3geyj104v-panasonic-55421973
1,P100GCT-ND,Panasonic,ERJ-3GEYJ101V,https://octopart.com/erj-3geyj101v-panasonic-55405017
1,RHM68DCT-ND,rohm,ESR03EZPJ680,https://octopart.com/esr03ezpj680-rohm-29236221
1,RHM180DCT-ND,rohm,ESR03EZPJ181,https://octopart.com/esr03ezpj181-rohm-19170366
15,MCT0603-10.0K-CFCT-ND,Vishay,MCT06030C1002FP500,https://octopart.com/mct06030c1002fp500-vishay-55388462
1,490-2436-1-ND,Murata,NCP18XH103J03RB,https://octopart.com/ncp18xh103j03rb-murata-745856
1,RHM10DCT-ND,rohm,ESR03EZPJ100,https://octopart.com/esr03ezpj100-rohm-19170060
4,1276-4751-1-ND,Samsung,RC1608F1212CS,https://octopart.com/rc1608f1212cs-samsung-9300780
1,MCT0603-15.0K-CFCT-ND,Vishay,MCT06030C1502FP500,https://octopart.com/mct06030c1502fp500-vishay-43439988
27,MCT0603-1.00K-CFCT-ND,Vishay,MCT06030C1001FP500,https://octopart.com/mct06030c1001fp500-vishay-46566501
2,311-22.1HRCT-ND,Yageo,RC0603FR-0722R1L,https://octopart.com/rc0603fr-0722r1l-yageo-1190988
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
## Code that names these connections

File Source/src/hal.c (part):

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//const Gpio_Pin RFID_INT             = { GPIOB, GPIO_Pin_5  };
//const Gpio_Pin FINGER_PRINT_BUTTON  = { GPIOB, GPIO_Pin_6  };

//const Gpio_Pin LOW_BAT              = { GPIOB, GPIO_Pin_8  };

//const Gpio_Pin DAC1					= { GPIOA, GPIO_PIN_4 };
//const Gpio_Pin DAC2					= { GPIOA, GPIO_PIN_5 };
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//CORRECT FOR PSDR1
const Gpio_Pin LCD_DC =
  { GPIOB, GPIO_PIN_7 }; //2.5
const Gpio_Pin LCD_RESET =
  { GPIOB, GPIO_PIN_6 }; //2.5
const Gpio_Pin LCD_NSS =
  { GPIOA, GPIO_PIN_15 }; //2.5 //When this was set wrong, the display still worked. No need?
const Gpio_Pin LCD_LED =
  { GPIOC, GPIO_PIN_13 }; //2.5
//const Gpio_Pin ddsReset 			= { GPIOC, GPIO_PIN_3 };
//const Gpio_Pin ddsSleep 			= { GPIOA, GPIO_PIN_0  };
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//const Gpio_Pin dds2Mosi 			= { GPIOE, GPIO_PIN_4  };
//const Gpio_Pin dds2Nss 				= { GPIOE, GPIO_PIN_6  };
//const Gpio_Pin dds2Sck 				= { GPIOE, GPIO_PIN_5  };
const Gpio_Pin LCD_MOSI =
  { GPIOB, GPIO_PIN_5 }; //2.5
const Gpio_Pin LCD_MISO =
  { GPIOB, GPIO_PIN_4 }; //2.5
const Gpio_Pin LCD_SCK =
  { GPIOB, GPIO_PIN_3 }; //2.5
const Gpio_Pin encoderBee =
  { GPIOE, GPIO_PIN_0 }; //2.5
const Gpio_Pin encoderB =
  { GPIOE, GPIO_PIN_1 }; //2.5 (really ENC_A)
const Gpio_Pin encoderP =
  { GPIOB, GPIO_PIN_9 }; //2.5
const Gpio_Pin RX_Q =
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//  { GPIOB, GPIO_PIN_15 };
//const Gpio_Pin TX_MUX =
//  { GPIOB, GPIO_PIN_14 };
const Gpio_Pin AMP_SWITCH_A =
  { GPIOA, GPIO_PIN_0 }; //2.5
const Gpio_Pin AMP_SWITCH_B =
  { GPIOE, GPIO_PIN_6 }; //2.5
const Gpio_Pin IMP_BRIDGE_SWITCH_A =
  { GPIOC, GPIO_PIN_1 }; //2.5
const Gpio_Pin IMP_BRIDGE_SWITCH_B =
  { GPIOA, GPIO_PIN_6 }; //2.5
//const Gpio_Pin MIXER_SWITCH_A =
//  { GPIOE, GPIO_PIN_13 };
//const Gpio_Pin MIXER_SWITCH_B =
//  { GPIOE, GPIO_PIN_14 };
const Gpio_Pin TX_RF_SWITCH_A =
  { GPIOB, GPIO_PIN_2 }; //2.5
const Gpio_Pin TX_RF_SWITCH_B =
  { GPIOA, GPIO_PIN_7 }; //2.5

const Gpio_Pin AMP_POWER =
  { GPIOE, GPIO_PIN_3 }; //2.5
//const Gpio_Pin MIXER_POWER =
//  { GPIOE, GPIO_PIN_10 };
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  { GPIOB, GPIO_PIN_13 }; //2.5
const Gpio_Pin FILTER_GAIN_POT_MOSI =
  { GPIOB, GPIO_PIN_15 }; //2.5
const Gpio_Pin GAIN_POT_NSS =
  { GPIOE, GPIO_PIN_5 }; //2.5

const Gpio_Pin DAC_MUX =
  { GPIOE, GPIO_PIN_4 }; //2.5

const Gpio_Pin AUDIO_AMP_NSHTDWN =
  { GPIOE, GPIO_PIN_14 }; //2.5
const Gpio_Pin EARPHONE_NOT_INSERTED =
  { GPIOD, GPIO_PIN_11 }; //2.5
const Gpio_Pin SIDETONE =
  { GPIOD, GPIO_PIN_12 }; //2.5 //Should be a timer pin.

const Gpio_Pin MIC_IN =
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const Gpio_Pin PREAMP_POWER =
  { GPIOD, GPIO_PIN_14 }; //2.5

const Gpio_Pin PADDLE_THUMB_NO =
  { GPIOD, GPIO_PIN_3 }; //2.5
const Gpio_Pin PADDLE_INDEX_NO =
  { GPIOD, GPIO_PIN_7 }; //2.5
const Gpio_Pin PADDLE_THUMB_NC =
  { GPIOD, GPIO_PIN_5 }; //2.5
const Gpio_Pin PADDLE_INDEX_NC =
  { GPIOD, GPIO_PIN_6 }; //2.5


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//const Gpio_Pin GSM_NRST             = { GPIOA, GPIO_Pin_12 };
//const Gpio_Pin GSM_STATUS           = { GPIOC, GPIO_Pin_9  };
//const Gpio_Pin SERVO_PWR            = { GPIOC, GPIO_Pin_10 };
//const Gpio_Pin CHARGE_STATUS2       = { GPIOC, GPIO_Pin_13 };
//const Gpio_Pin POWER_GOOD           = { GPIOC, GPIO_Pin_14 };
//const Gpio_Pin POWER_SWITCH         = { GPIOC, GPIO_Pin_15 };
//const Gpio_Pin ACCEL_NSS            = { GPIOD, GPIO_Pin_2  };   // currently labeled SPI2_NSS on schem
const Gpio_Pin GPS_RESET =
  { GPIOE, GPIO_PIN_15 }; //2.5
//const Gpio_Pin GPS_FIX_LED =
//  { GPIOE, GPIO_PIN_15 }; //2.5
const Gpio_Pin GPS_PPS =
  { GPIOE, GPIO_PIN_7 }; //2.5
const Gpio_Pin GPS_POWER =
  { GPIOA, GPIO_PIN_8 }; //2.5
const Gpio_Pin RX_TO_GPS =
  { GPIOC, GPIO_PIN_6 }; //2.5
const Gpio_Pin TX_FROM_GPS =
  { GPIOC, GPIO_PIN_7 }; //2.5


const Gpio_Pin IN_AMP_ENABLE =
  { GPIOC, GPIO_PIN_2 }; //2.5

const Gpio_Pin FILTER_S0 =
    { GPIOE, GPIO_PIN_10 }; //2.5
const Gpio_Pin FILTER_S1 =
    { GPIOD, GPIO_PIN_8  }; //2.5

const Gpio_Pin TRX_SWITCH =
    { GPIOC, GPIO_PIN_3  }; //2.5

const Gpio_Pin I2C_SCL =
    { GPIOB, GPIO_PIN_10 };
const Gpio_Pin I2C_SDA =
    { GPIOB, GPIO_PIN_11 };

const Gpio_Pin FLIP_FLOP_ENABLE =
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//    gpioInitStructure.GPIO_Mode  = GPIO_Mode_Out_PP;
//    GPIO_Init(LCD_DC.port, &gpioInitStructure);

  gpioInitStructure.Pin = LCD_RESET.pin;
  gpioInitStructure.Speed = GPIO_SPEED_FAST;
  gpioInitStructure.Mode = GPIO_MODE_OUTPUT_PP;
  gpioInitStructure.Alternate = 0;
  gpioInitStructure.Pull = GPIO_NOPULL;
  HAL_GPIO_Init (LCD_RESET.port, &gpioInitStructure);

  gpioInitStructure.Pin = LCD_LED.pin;
  gpioInitStructure.Speed = GPIO_SPEED_LOW;
  gpioInitStructure.Mode = GPIO_MODE_OUTPUT_OD;
  gpioInitStructure.Alternate = 0;
  gpioInitStructure.Pull = GPIO_NOPULL;
  HAL_GPIO_Init (LCD_LED.port, &gpioInitStructure);
  HAL_GPIO_WritePin (LCD_LED.port, LCD_LED.pin, 0);

  // 'DAC' switches
//    gpioInitStructure.GPIO_Pin   = DAC_SWITCHES.pin;
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//  HAL_GPIO_Init (TX_MUX.port, &gpioInitStructure);
//  HAL_GPIO_WritePin (TX_MUX.port, TX_MUX.pin, 0); //Active Low

  gpioInitStructure.Pin = TX_RF_SWITCH_A.pin;
  gpioInitStructure.Mode = GPIO_MODE_OUTPUT_PP;
  gpioInitStructure.Speed = GPIO_SPEED_LOW;
  gpioInitStructure.Pull = GPIO_NOPULL;
  HAL_GPIO_Init (TX_RF_SWITCH_A.port, &gpioInitStructure);
  HAL_GPIO_WritePin (TX_RF_SWITCH_A.port, TX_RF_SWITCH_A.pin, 1); //0 to route to TX SMA connector

  gpioInitStructure.Pin = TX_RF_SWITCH_B.pin;
  gpioInitStructure.Mode = GPIO_MODE_OUTPUT_PP;
  gpioInitStructure.Speed = GPIO_SPEED_LOW;
  gpioInitStructure.Pull = GPIO_NOPULL;
  HAL_GPIO_Init (TX_RF_SWITCH_B.port, &gpioInitStructure);
  HAL_GPIO_WritePin (TX_RF_SWITCH_B.port, TX_RF_SWITCH_B.pin, 0); //always reverse of above.

//  gpioInitStructure.Pin = MIXER_SWITCH_A.pin;
//  gpioInitStructure.Mode = GPIO_MODE_OUTPUT_PP;
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//  HAL_GPIO_Init (MIXER_SWITCH_B.port, &gpioInitStructure);
//  HAL_GPIO_WritePin (MIXER_SWITCH_B.port, MIXER_SWITCH_B.pin, 1); //always reverse of above.

  gpioInitStructure.Pin = IMP_BRIDGE_SWITCH_A.pin;
  gpioInitStructure.Mode = GPIO_MODE_OUTPUT_PP;
  gpioInitStructure.Speed = GPIO_SPEED_LOW;
  gpioInitStructure.Pull = GPIO_NOPULL;
  HAL_GPIO_Init (IMP_BRIDGE_SWITCH_A.port, &gpioInitStructure);
  HAL_GPIO_WritePin (IMP_BRIDGE_SWITCH_A.port, IMP_BRIDGE_SWITCH_A.pin, 0); //always reverse of above.

  gpioInitStructure.Pin = IMP_BRIDGE_SWITCH_B.pin;
  gpioInitStructure.Mode = GPIO_MODE_OUTPUT_PP;
  gpioInitStructure.Speed = GPIO_SPEED_LOW;
  gpioInitStructure.Pull = GPIO_NOPULL;
  HAL_GPIO_Init (IMP_BRIDGE_SWITCH_B.port, &gpioInitStructure);
  HAL_GPIO_WritePin (IMP_BRIDGE_SWITCH_B.port, IMP_BRIDGE_SWITCH_B.pin, 1); //always reverse of above.

  gpioInitStructure.Pin = AMP_SWITCH_A.pin;
  gpioInitStructure.Mode = GPIO_MODE_OUTPUT_PP;
  gpioInitStructure.Speed = GPIO_SPEED_LOW;
  gpioInitStructure.Pull = GPIO_NOPULL;
  HAL_GPIO_Init (AMP_SWITCH_A.port, &gpioInitStructure);
  HAL_GPIO_WritePin (AMP_SWITCH_A.port, AMP_SWITCH_A.pin, 0); //always reverse of above.

  gpioInitStructure.Pin = AMP_SWITCH_B.pin;
  gpioInitStructure.Mode = GPIO_MODE_OUTPUT_PP;
  gpioInitStructure.Speed = GPIO_SPEED_LOW;
  gpioInitStructure.Pull = GPIO_NOPULL;
  HAL_GPIO_Init (AMP_SWITCH_B.port, &gpioInitStructure);
  HAL_GPIO_WritePin (AMP_SWITCH_B.port, AMP_SWITCH_B.pin, 1); //always reverse of above.
//
//  gpioInitStructure.Pin = MIXER_POWER.pin;
//  gpioInitStructure.Mode = GPIO_MODE_OUTPUT_OD;
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//  HAL_GPIO_Init (MIXER_POWER.port, &gpioInitStructure);
//  HAL_GPIO_WritePin (MIXER_POWER.port, MIXER_POWER.pin, 1); //1 is off.

  gpioInitStructure.Pin = AMP_POWER.pin;
  gpioInitStructure.Mode = GPIO_MODE_OUTPUT_OD;
  gpioInitStructure.Speed = GPIO_SPEED_LOW;
  gpioInitStructure.Pull = GPIO_PULLUP;
  HAL_GPIO_Init (AMP_POWER.port, &gpioInitStructure);
  HAL_GPIO_WritePin (AMP_POWER.port, AMP_POWER.pin, 1); //1 is off.

  gpioInitStructure.Pin = FILTER_GAIN_POT_MOSI.pin;
  gpioInitStructure.Mode = GPIO_MODE_OUTPUT_PP;
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  HAL_GPIO_Init (FILTER_GAIN_POT_SCLK.port, &gpioInitStructure);
  HAL_GPIO_WritePin (FILTER_GAIN_POT_SCLK.port, FILTER_GAIN_POT_SCLK.pin, 1);

  gpioInitStructure.Pin = GAIN_POT_NSS.pin;
  gpioInitStructure.Mode = GPIO_MODE_OUTPUT_PP;
  gpioInitStructure.Speed = GPIO_SPEED_LOW;
  gpioInitStructure.Pull = GPIO_NOPULL;
  HAL_GPIO_Init (GAIN_POT_NSS.port, &gpioInitStructure);
  HAL_GPIO_WritePin (GAIN_POT_NSS.port, GAIN_POT_NSS.pin, 1);

  gpioInitStructure.Pin = DAC_MUX.pin;
  gpioInitStructure.Mode = GPIO_MODE_OUTPUT_PP;
  gpioInitStructure.Speed = GPIO_SPEED_LOW;
  gpioInitStructure.Pull = GPIO_NOPULL;
  HAL_GPIO_Init (DAC_MUX.port, &gpioInitStructure);
  HAL_GPIO_WritePin (DAC_MUX.port, DAC_MUX.pin, 1); //0 = speaker/earphone. Speaker doesn't seem to work, btw...

//    	gpioInitStructure.Pin = EARPHONE_NOT_INSERTED.pin;
//    	gpioInitStructure.Mode = GPIO_MODE_ANALOG;
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  HAL_GPIO_Init (AUDIO_AMP_NSHTDWN.port, &gpioInitStructure);
  HAL_GPIO_WritePin (AUDIO_AMP_NSHTDWN.port, AUDIO_AMP_NSHTDWN.pin, 1);

  gpioInitStructure.Pin = SIDETONE.pin;
  gpioInitStructure.Mode = GPIO_MODE_ANALOG; //For now, or when not in use.
  gpioInitStructure.Speed = GPIO_SPEED_LOW;
  gpioInitStructure.Pull = GPIO_NOPULL;
  HAL_GPIO_Init (SIDETONE.port, &gpioInitStructure);
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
